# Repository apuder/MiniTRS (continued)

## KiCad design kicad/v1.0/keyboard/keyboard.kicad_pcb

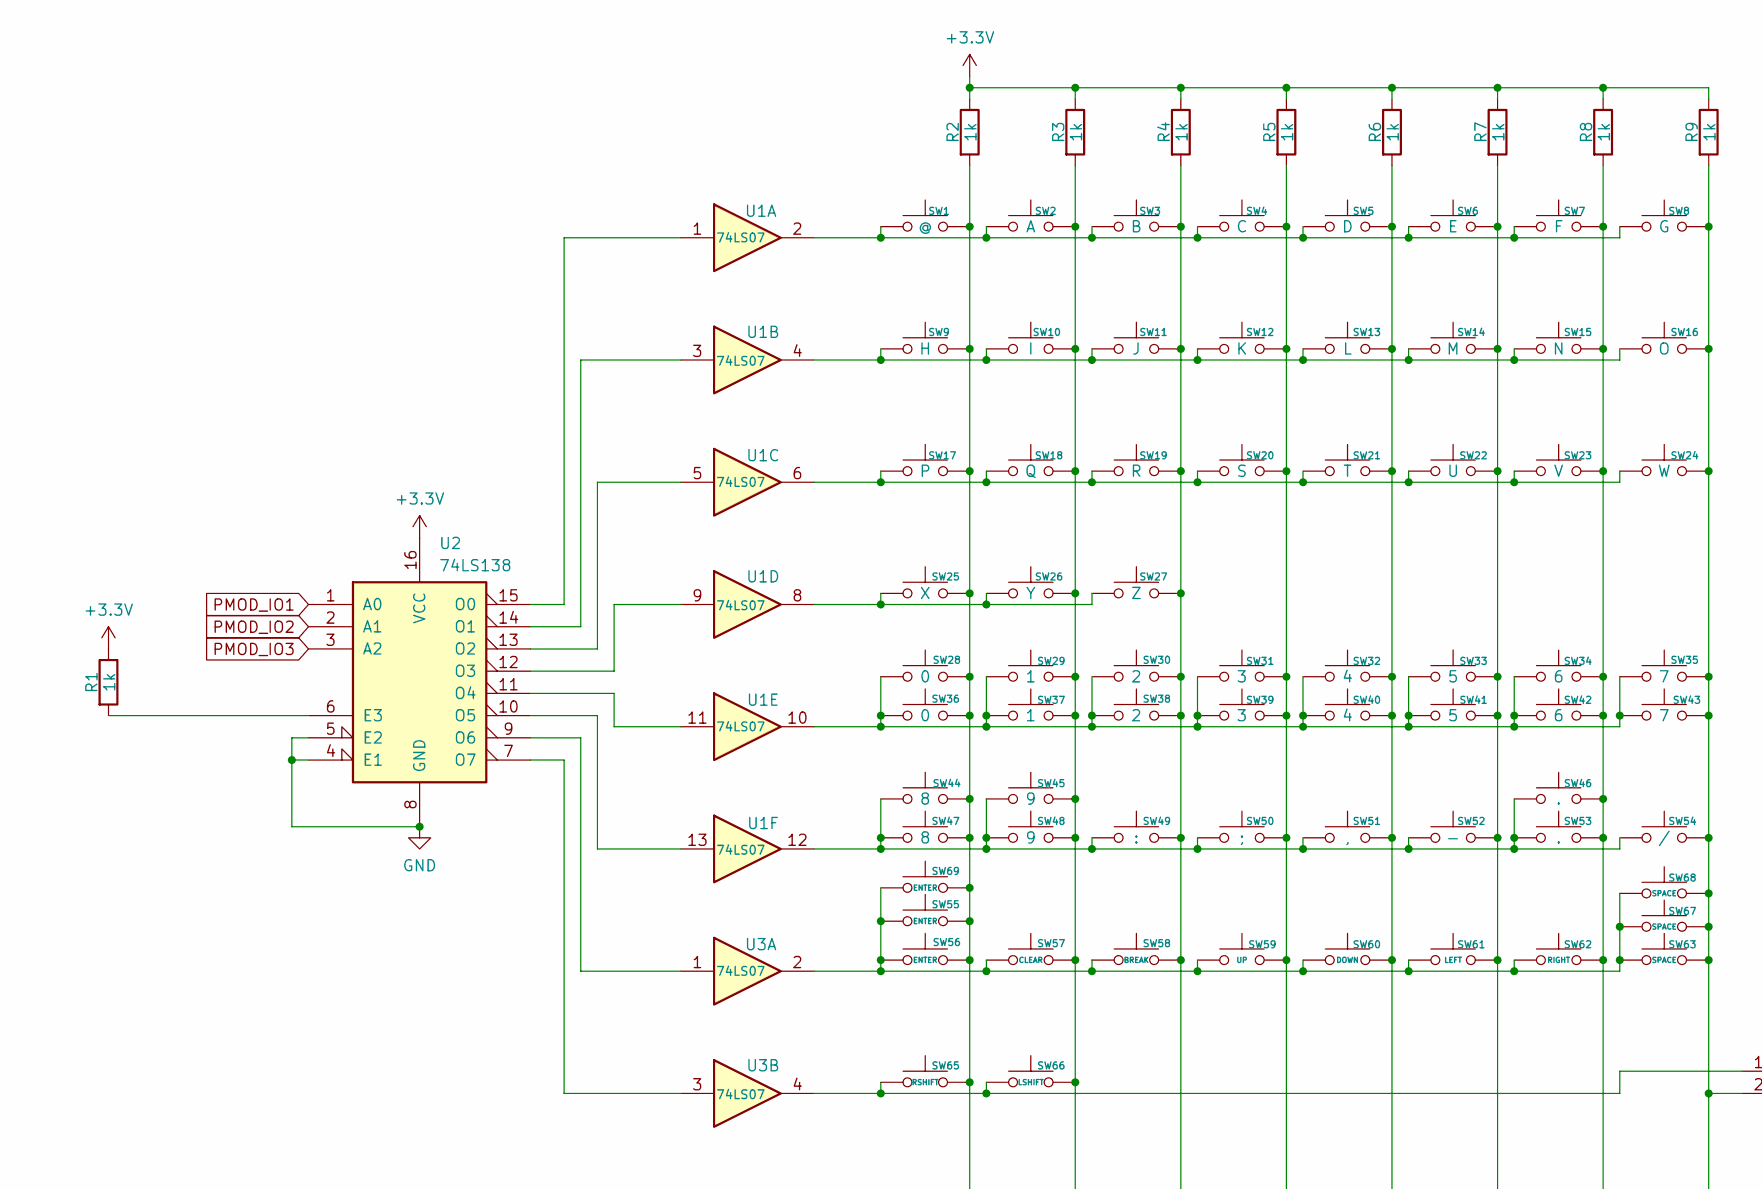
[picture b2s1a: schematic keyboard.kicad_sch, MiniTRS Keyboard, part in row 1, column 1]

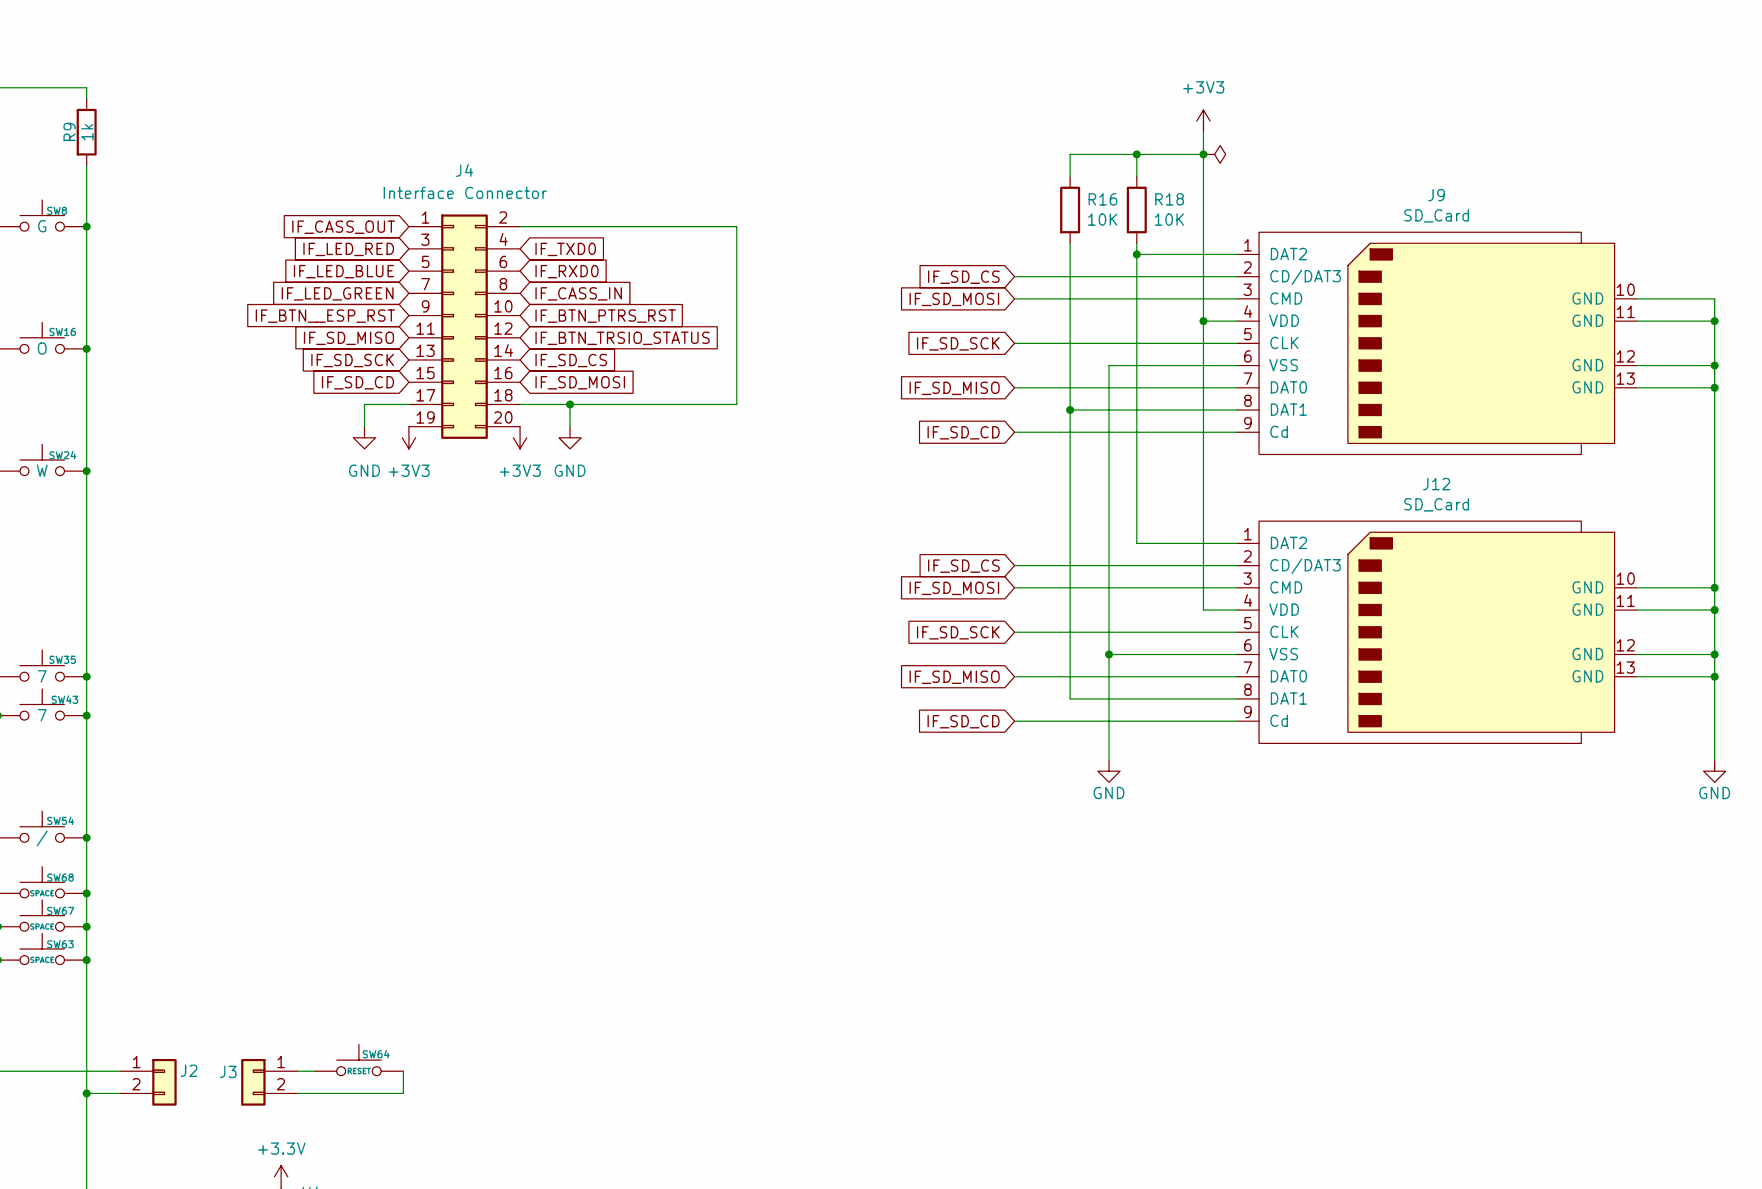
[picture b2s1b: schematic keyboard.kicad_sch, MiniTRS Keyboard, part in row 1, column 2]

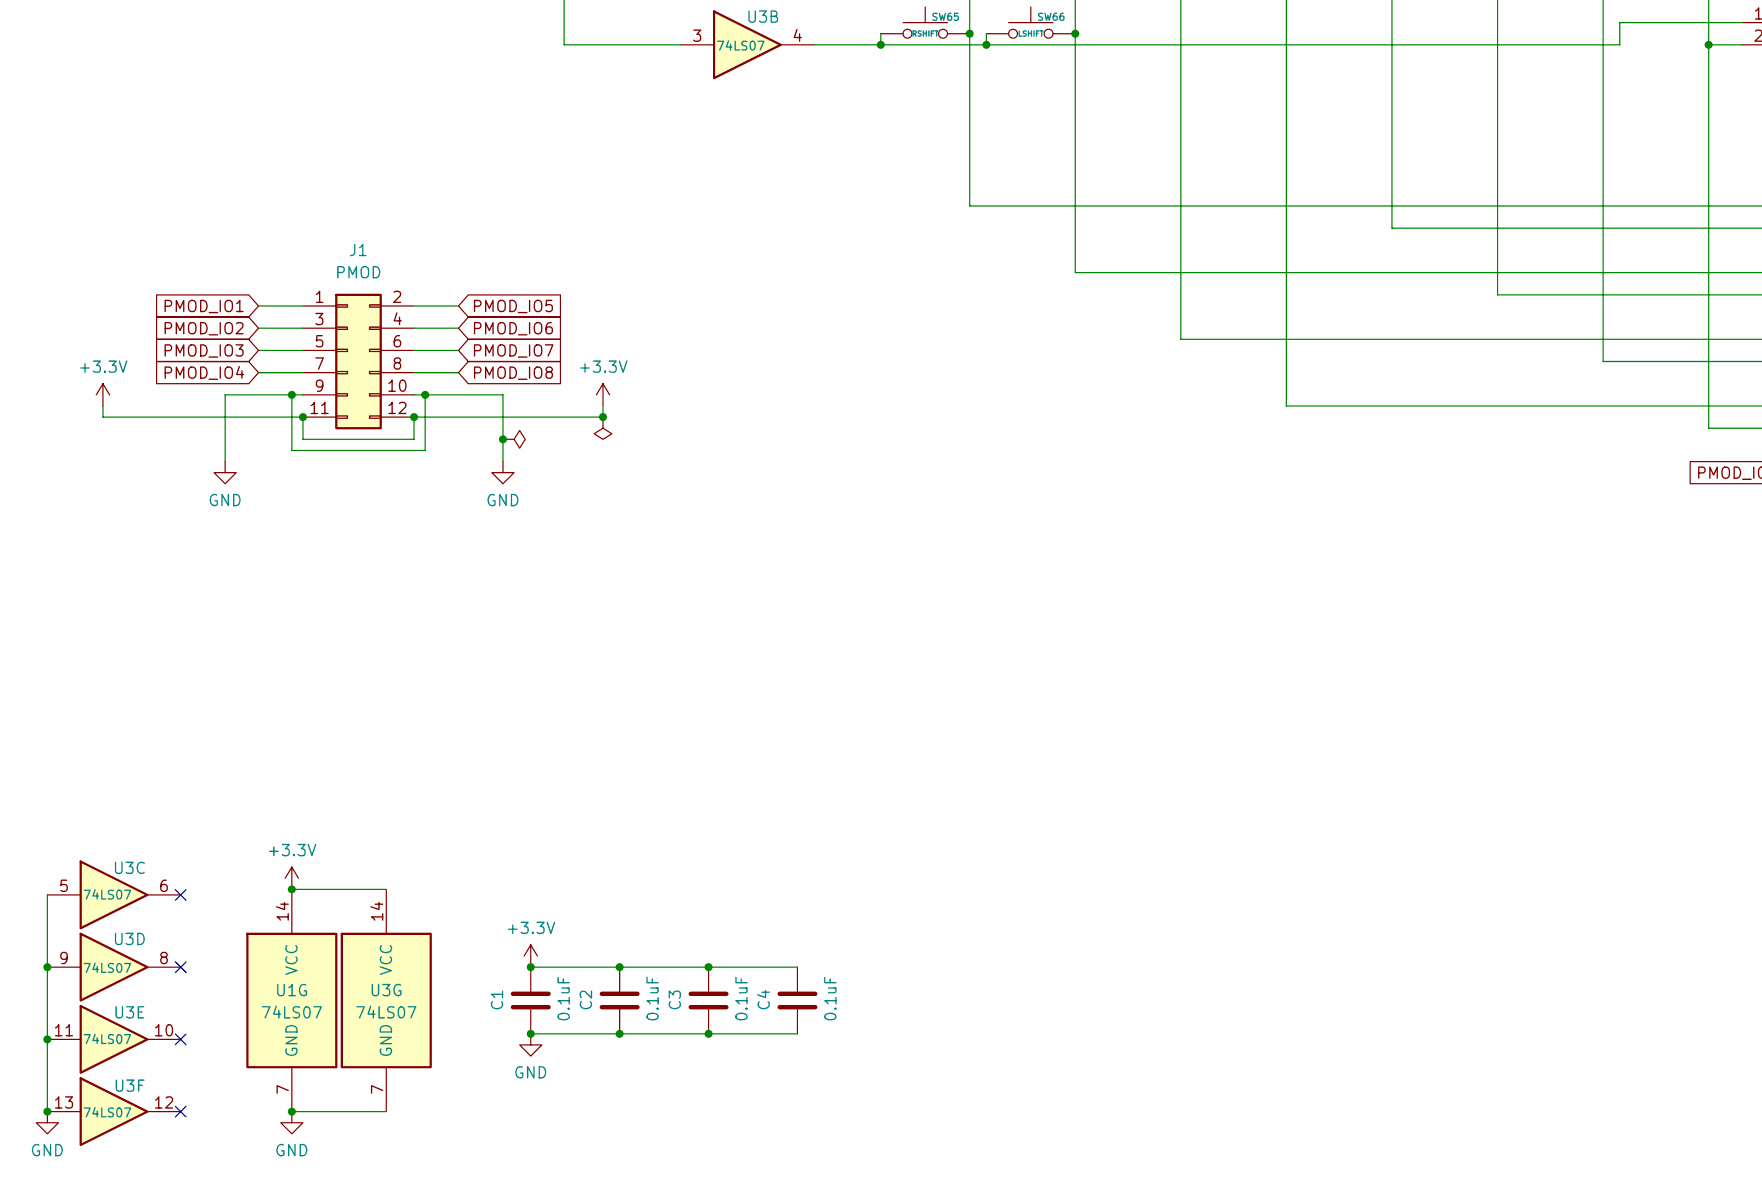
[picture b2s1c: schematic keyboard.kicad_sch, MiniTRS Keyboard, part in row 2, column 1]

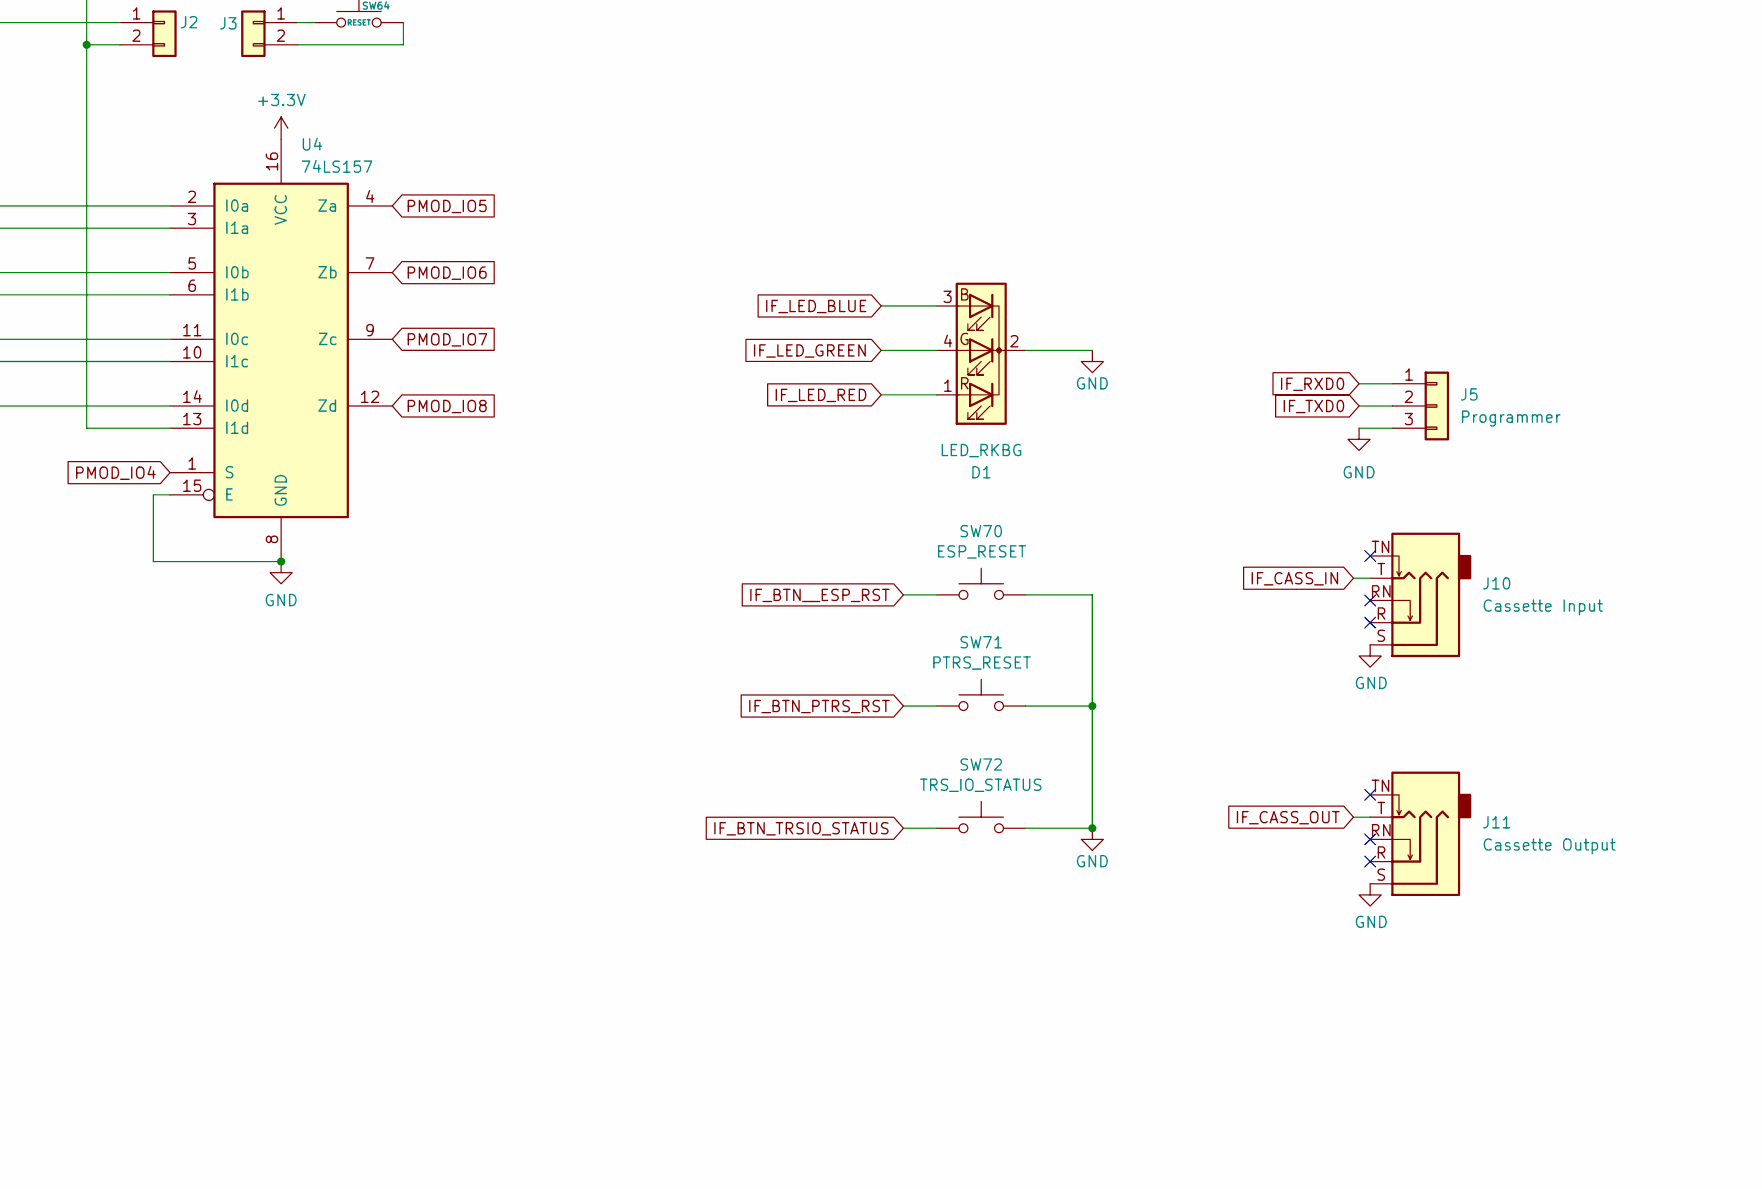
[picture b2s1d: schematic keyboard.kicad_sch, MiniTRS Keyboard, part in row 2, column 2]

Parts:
C1, C2, C3, C4: 0.1uF; C_0805_2012Metric_Pad1.18x1.45mm_HandSolder
D1: LED_RKBG; LED_D5.0mm-4_RGB
J1: PMOD; PinSocket_2x06_P2.54mm_Vertical; LCSC C358728
J2, J3: Conn_01x02; PinHeader_1x02_P2.54mm_Vertical
J4: Interface Connector; PinHeader_2x10_P1.27mm_Vertical
J5: Programmer; PinHeader_1x03_P2.54mm_Horizontal
J9, J12: SD_Card; TFP09-2-12B; LCSC C19189038
J10: Cassette Input; Jack_3.5mm_CUI_SJ1-3525N_Horizontal
J11: Cassette Output; Jack_3.5mm_CUI_SJ1-3525N_Horizontal
R1, R2, R3, R4, R5, R6, R7, R8, R9: 1k; R_0805_2012Metric_Pad1.20x1.40mm_HandSolder
R16, R18: 10K; R_0805_2012Metric_Pad1.20x1.40mm_HandSolder
SW1: @; SW_SPST_Push
SW2: A; SW_SPST_Push
SW3: B; SW_SPST_Push
SW4: C; SW_SPST_Push
SW5: D; SW_SPST_Push
SW6: E; SW_SPST_Push
SW7: F; SW_SPST_Push
SW8: G; SW_SPST_Push
SW9: H; SW_SPST_Push
SW10: I; SW_SPST_Push
SW11: J; SW_SPST_Push
SW12: K; SW_SPST_Push
SW13: L; SW_SPST_Push
SW14: M; SW_SPST_Push
SW15: N; SW_SPST_Push
SW16: O; SW_SPST_Push
SW17: P; SW_SPST_Push
SW18: Q; SW_SPST_Push
SW19: R; SW_SPST_Push
SW20: S; SW_SPST_Push
SW21: T; SW_SPST_Push
SW22: U; SW_SPST_Push
SW23: V; SW_SPST_Push
SW24: W; SW_SPST_Push
SW25: X; SW_SPST_Push
SW26: Y; SW_SPST_Push
SW27: Z; SW_SPST_Push
SW28, SW36: 0; SW_SPST_Push
SW29, SW37: 1; SW_SPST_Push
SW30, SW38: 2; SW_SPST_Push
SW31, SW39: 3; SW_SPST_Push
SW32, SW40: 4; SW_SPST_Push
SW33, SW41: 5; SW_SPST_Push
SW34, SW42: 6; SW_SPST_Push
SW35, SW43: 7; SW_SPST_Push
SW44, SW47: 8; SW_SPST_Push
SW45, SW48: 9; SW_SPST_Push
SW46, SW53: .; SW_SPST_Push
SW49: :; SW_SPST_Push
SW50: ;; SW_SPST_Push
SW51: ,; SW_SPST_Push
SW52: -; SW_SPST_Push
SW54: /; SW_SPST_Push
SW55, SW56, SW69: ENTER; SW_SPST_Push
SW57: CLEAR; SW_SPST_Push
SW58: BREAK; SW_SPST_Push
SW59: UP; SW_SPST_Push
SW60: DOWN; SW_SPST_Push
SW61: LEFT; SW_SPST_Push
SW62: RIGHT; SW_SPST_Push
SW63, SW67, SW68: SPACE; SW_SPST_Push
SW64: RESET; SW_SPST_Push
SW65: RSHIFT; SW_SPST_Push
SW66: LSHIFT; SW_SPST_Push
SW70: ESP_RESET; SW_Tactile_SPST_Angled_PTS645Vx83-2LFS; LCSC C722960
SW71: PTRS_RESET; SW_Tactile_SPST_Angled_PTS645Vx83-2LFS; LCSC C722960
SW72: TRS_IO_STATUS; SW_Tactile_SPST_Angled_PTS645Vx83-2LFS; LCSC C722960
U1, U3: 74LS07; SOIC-14_3.9x8.7mm_P1.27mm
U2: 74LS138; SOIC-16_3.9x9.9mm_P1.27mm
U4: 74LS157; SOIC-16_3.9x9.9mm_P1.27mm

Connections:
+3.3V: C1.1, C2.1, C3.1, C4.1, J1.11, J1.12, R1.1, R2.1, R3.1, R4.1, R5.1, R6.1, R7.1, R8.1, R9.1, U1.14 (VCC), U2.16 (VCC), U3.14 (VCC), U4.16 (VCC)
+3V3: J4.19, J4.20, J9.4 (VDD), J12.4 (VDD), R16.1, R18.1
GND: C1.2, C2.2, C3.2, C4.2, D1.2 (K), J1.9, J1.10, J4.2, J4.17, J4.18, J5.3, J9.6 (VSS), J9.10 (GND), J9.11 (GND), J9.12 (GND), J9.13 (GND), J10.S, J11.S, J12.6 (VSS), J12.10 (GND), J12.11 (GND), J12.12 (GND), J12.13 (GND), SW70.2, SW71.2, SW72.2, U1.7 (GND), U2.4 (E1), U2.5 (E2), U2.8 (GND), U3.5, U3.7 (GND), U3.9, U3.11, U3.13, U4.8 (GND), U4.15 (E)
IF_BTN_PTRS_RST: J4.10, SW71.1
IF_BTN_TRSIO_STATUS: J4.12, SW72.1
IF_BTN__ESP_RST: J4.9, SW70.1
IF_CASS_IN: J4.8, J10.T
IF_CASS_OUT: J4.1, J11.T
IF_LED_BLUE: D1.3 (BA), J4.5
IF_LED_GREEN: D1.4 (GA), J4.7
IF_LED_RED: D1.1 (RA), J4.3
IF_RXD0: J4.6, J5.1
IF_SD_CD: J4.15, J9.9 (Cd), J12.9 (Cd)
IF_SD_CS: J4.14, J9.2 (CD/DAT3), J12.2 (CD/DAT3)
IF_SD_MISO: J4.11, J9.7 (DAT0), J12.7 (DAT0)
IF_SD_MOSI: J4.16, J9.3 (CMD), J12.3 (CMD)
IF_SD_SCK: J4.13, J9.5 (CLK), J12.5 (CLK)
IF_TXD0: J4.4, J5.2
unnamed: J2.1, SW65.1, SW66.2, U3.4
unnamed: J2.2, R9.2, SW8.1, SW16.2, SW24.1, SW35.2, SW43.1, SW54.1, SW63.1, SW67.1, SW68.1, U4.13 (I1d)
unnamed: J3.1, SW64.2
unnamed: J3.2, SW64.1
unnamed: J9.8 (DAT1), J12.8 (DAT1), R16.2
unnamed: J9.1 (DAT2), J12.1 (DAT2), R18.2
unnamed: SW1.2, SW2.1, SW3.2, SW4.2, SW5.1, SW6.1, SW7.1, SW8.2, U1.2
unnamed: SW9.2, SW10.2, SW11.2, SW12.1, SW13.2, SW14.1, SW15.1, SW16.1, U1.4
unnamed: SW17.2, SW18.2, SW19.1, SW20.1, SW21.1, SW22.1, SW23.1, SW24.2, U1.6
unnamed: SW25.1, SW26.2, SW27.2, U1.8
unnamed: SW28.2, SW29.2, SW30.1, SW31.2, SW32.2, SW33.2, SW34.2, SW35.1, SW36.1, SW37.2, SW38.1, SW39.2, SW40.2, SW41.2, SW42.2, SW43.2, U1.10
unnamed: SW44.2, SW45.2, SW46.1, SW47.1, SW48.2, SW49.1, SW50.1, SW51.1, SW52.2, SW53.1, SW54.2, U1.12
unnamed: SW55.1, SW56.2, SW57.1, SW58.1, SW59.1, SW60.2, SW61.1, SW62.2, SW63.2, SW67.2, SW68.2, SW69.1, U3.2
unnamed: R1.2, U2.6 (E3)
unnamed: U1.1, U2.15 (O0)
unnamed: U1.3, U2.14 (O1)
unnamed: U1.5, U2.13 (O2)
unnamed: U1.9, U2.12 (O3)
unnamed: U1.11, U2.11 (O4)
unnamed: U1.13, U2.10 (O5)
unnamed: U2.9 (O6), U3.1
unnamed: U2.7 (O7), U3.3
unnamed: R2.2, SW1.1, SW9.1, SW17.1, SW25.2, SW28.1, SW36.2, SW44.1, SW47.2, SW55.2, SW56.1, SW65.2, SW69.2, U4.2 (I0a)
unnamed: R3.2, SW2.2, SW10.1, SW18.1, SW26.1, SW29.1, SW37.1, SW45.1, SW48.1, SW57.2, SW66.1, U4.5 (I0b)
unnamed: R4.2, SW3.1, SW11.1, SW19.2, SW27.1, SW30.2, SW38.2, SW49.2, SW58.2, U4.11 (I0c)
unnamed: R5.2, SW4.1, SW12.2, SW20.2, SW31.1, SW39.1, SW50.2, SW59.2, U4.14 (I0d)
unnamed: R6.2, SW5.2, SW13.1, SW21.2, SW32.1, SW40.1, SW51.2, SW60.1, U4.3 (I1a)
unnamed: R7.2, SW6.2, SW14.2, SW22.2, SW33.1, SW41.1, SW52.1, SW61.2, U4.6 (I1b)
unnamed: R8.2, SW7.2, SW15.2, SW23.2, SW34.1, SW42.1, SW46.2, SW53.2, SW62.1, U4.10 (I1c)
PMOD_IO1: J1.1, U2.1 (A0)
PMOD_IO2: J1.3, U2.2 (A1)
PMOD_IO3: J1.5, U2.3 (A2)
PMOD_IO4: J1.7, U4.1 (S)
PMOD_IO5: J1.2, U4.4 (Za)
PMOD_IO6: J1.4, U4.7 (Zb)
PMOD_IO7: J1.6, U4.9 (Zc)
PMOD_IO8: J1.8, U4.12 (Zd)

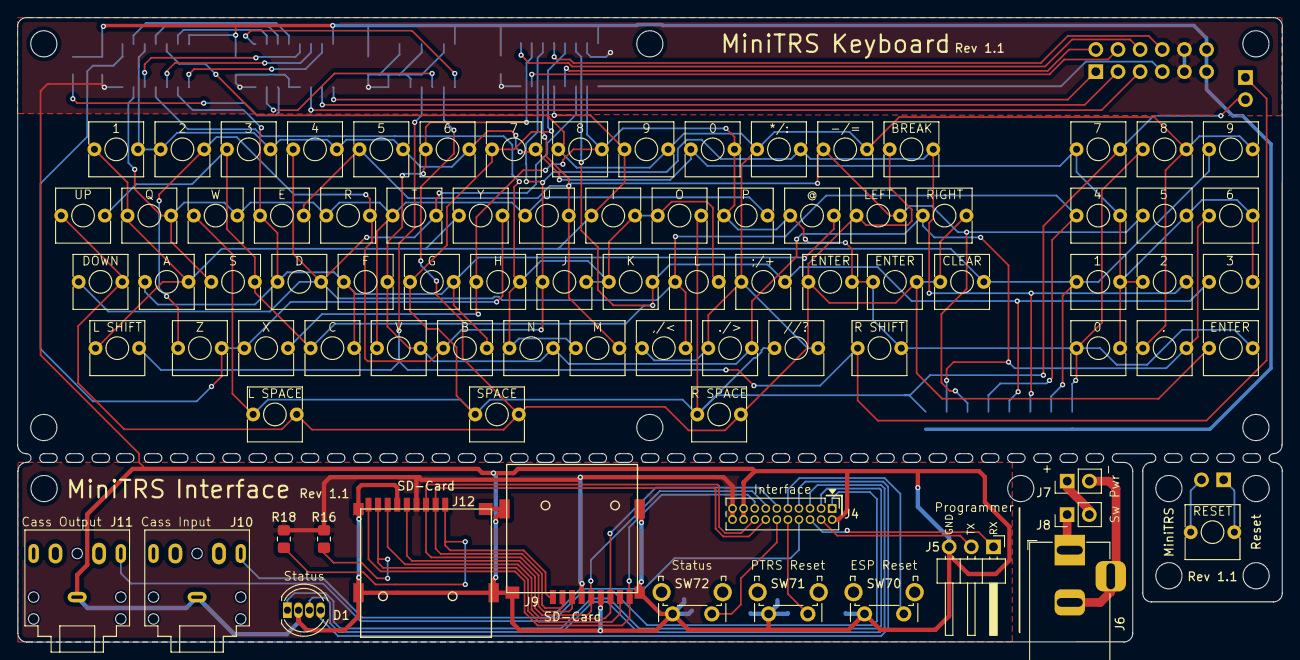
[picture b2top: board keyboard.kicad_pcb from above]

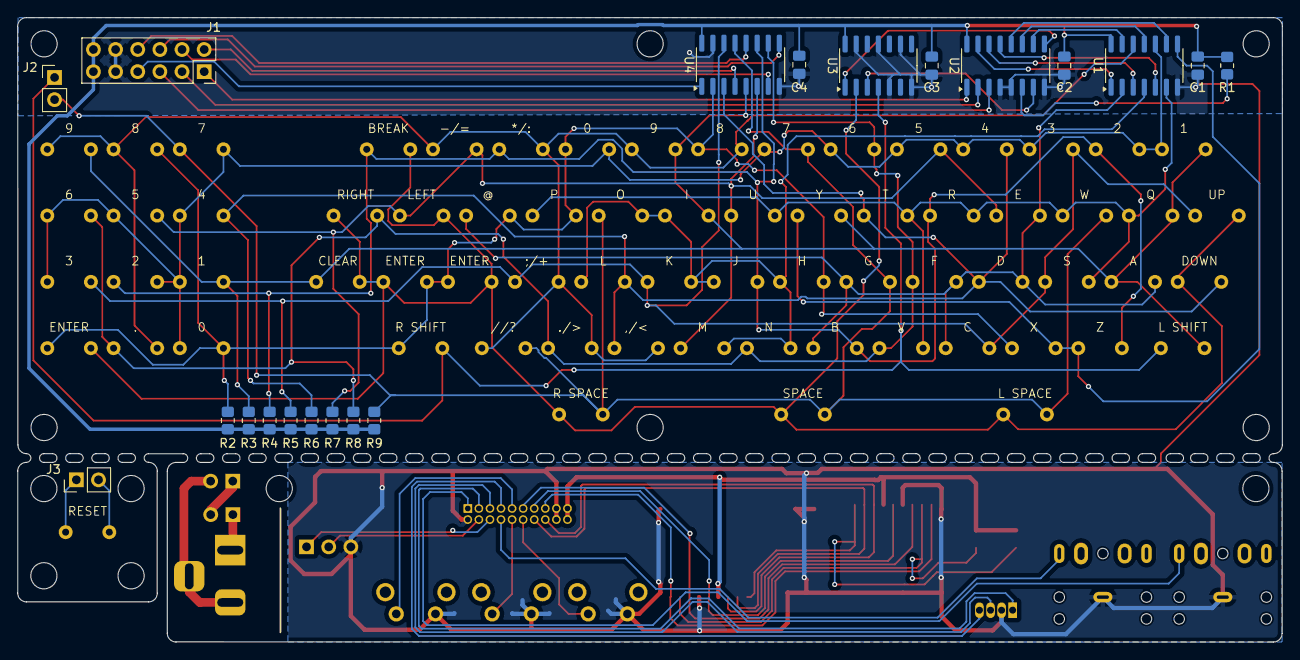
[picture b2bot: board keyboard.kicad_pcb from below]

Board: 2 copper layers, 145.0 x 71.6 mm, 104 parts (20 on the bottom side), 58 nets.

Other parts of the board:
J6: Barrel_Jack_Switch; BarrelJack_Horizontal
J7: Pwr Supply; PinHeader_1x02_P2.54mm_Vertical
J8: Pwr Switch; PinHeader_1x02_P2.54mm_Vertical

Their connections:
unnamed: J7.1, J8.2
unnamed: J6.2, J6.3, J7.2
unnamed: J6.1, J8.1

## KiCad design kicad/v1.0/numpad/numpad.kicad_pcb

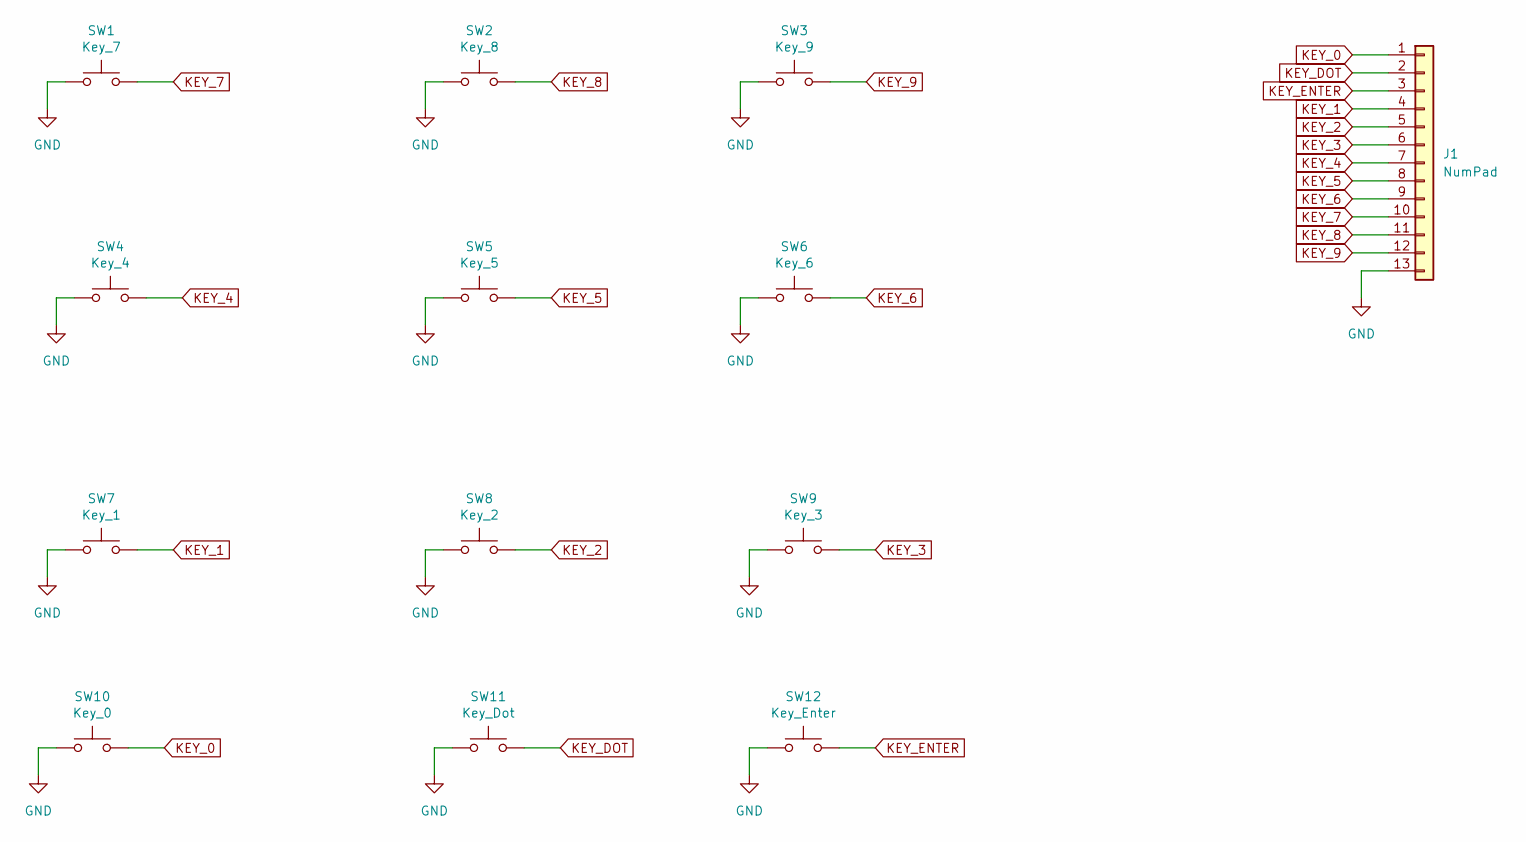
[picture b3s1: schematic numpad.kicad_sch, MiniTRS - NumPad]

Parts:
J1: NumPad; PinHeader_1x13_P2.54mm_Vertical
SW1: Key_7; SW_PUSH_6mm; LCSC C722960
SW2: Key_8; SW_PUSH_6mm; LCSC C722960
SW3: Key_9; SW_PUSH_6mm; LCSC C722960
SW4: Key_4; SW_PUSH_6mm; LCSC C722960
SW5: Key_5; SW_PUSH_6mm; LCSC C722960
SW6: Key_6; SW_PUSH_6mm; LCSC C722960
SW7: Key_1; SW_PUSH_6mm; LCSC C722960
SW8: Key_2; SW_PUSH_6mm; LCSC C722960
SW9: Key_3; SW_PUSH_6mm; LCSC C722960
SW10: Key_0; SW_PUSH_6mm; LCSC C722960
SW11: Key_Dot; SW_PUSH_6mm; LCSC C722960
SW12: Key_Enter; SW_PUSH_6mm; LCSC C722960

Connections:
GND: J1.13, SW1.1, SW2.1, SW3.1, SW4.1, SW5.1, SW6.1, SW7.1, SW8.1, SW9.1, SW10.1, SW11.1, SW12.1
KEY_0: J1.1, SW10.2
KEY_1: J1.4, SW7.2
KEY_2: J1.5, SW8.2
KEY_3: J1.6, SW9.2
KEY_4: J1.7, SW4.2
KEY_5: J1.8, SW5.2
KEY_6: J1.9, SW6.2
KEY_7: J1.10, SW1.2
KEY_8: J1.11, SW2.2
KEY_9: J1.12, SW3.2
KEY_DOT: J1.2, SW11.2
KEY_ENTER: J1.3, SW12.2

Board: 2 copper layers, 13 parts (0 on the bottom side), 13 nets, no tracks yet.

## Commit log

2025-06-15 Schematic for M3 keyboard
2025-06-15 Schematic for M3 numpad
2025-06-18 Positioning
    - Added Library
    - Created Footprint for 2-pin push-button
    - Added additional keys for ENTER and SPACE to cover whole length
    - Added keys for numpad (1:1 link to other number keys)
    - Positioned main keys, numpad keys
    - Created cutout for reset switch
2025-06-22 Redesign of Keyboard
    This is a new design of the keyboard that is based on the TRS-80 Model 1 keyboard interface design.
2025-06-23 Remove unneeded numpad
2025-06-23 Import TRS-IO++ schematics
2025-06-23 Add README
2025-06-28 Adding 3D Models
2025-07-03 Add ground pour (maboytim)
2025-07-04 Custom TRS-IO++ PCB (incomplete, no video)
2025-07-04 Badges and Labels
2025-07-04 Add footprints for SD card and audio jack
2025-07-04 Add schematics for interface PCB
2025-07-04 Update labels and add set
2025-07-21 Import of PTRS-M3 from TRS-IO++
2025-07-21 Add scanning of keyboard matrix
2025-08-05 Changed HDMI connector to 10 pin header.
2025-08-08 Updates to KiCad schematics/layout
2025-08-12 Converted cassette to mono in/out. Added audio amp.
2025-08-13 First version of PCB (without HDMI)
2025-08-14 Converted HDMI connector to SMD.
2025-08-14 First version of MiniTRS PCB
2025-08-18 Changed J4 connector for speaker
2025-08-19 Minor cleanup to PCB to improve ground fill.
2025-08-19 Add trimpot part number
2025-08-22 Update 3D Models with new keycap sizes
2025-08-28 Updated Interface board
2025-08-28 Rev 1.0 Gerber files for Keyboard
2025-08-30 New Models
    The case still needs the power plug
2025-08-31 Interface board with Barrel Jack for power
2025-08-31 Gerber files for rev 1.1 of keyboard/interface board
2025-08-31 Latest models for the case
2025-08-31 Add holes for stands
2025-08-31 Optimized keyboard bezel
2025-08-31 0.5 indentation at the bottom for keycaps
2025-09-01 M3 keyboard scanner
2025-09-12 New models with slight improvements
2025-09-19 Improved bottom and keyboard rig
2025-09-19 Templates and project for keyboard engraving
2025-09-22 Support for Reset key
2025-09-26 Update credits.
2025-09-26 Support setting of activity LEDs
2025-09-27 Update splash screen
2025-10-11 Original Label photos
2025-10-29 Kicad v1.1 of main PCB * Move SD card reader to seperate pin header * Remove DIP switch. Move DIP 4 to interface panel * Add PS/2 keyboard to interface panel
2025-11-02 Added hack to return different FDC status if queried from ROM. Added exlicit LVCMOS33 constraint to clk_in for newer compiler.
2026-02-05 V1.1 of PCB
